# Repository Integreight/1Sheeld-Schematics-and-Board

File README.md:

# 1Sheeld Schematics, Board and Fritzing part files #

## Overview ##

This repository contains the schematics, board, and Fritzing part files for 1Sheeld board.

## Schematics Reference Image ##

## Board Reference Image ##

## Fritzing Part Reference Image ##

## Changelog ##

To see what has changed in recent versions of 1Sheeld Schematics and Board files, see the [Change Log](CHANGELOG.md).

## License and Copyright ##

```
These files are free; you can redistribute them and/or modify them under the
terms of the Creative Commons Attribution-ShareAlike 4.0 International
License only, as published by the Creative Commons organization.

These files are distributed in the hope that they will be useful, but
WITHOUT ANY WARRANTY; without even the implied warranty of MERCHANTABILITY
or FITNESS FOR A PARTICULAR PURPOSE.  See the Creative Commons Attribution-
ShareAlike 4.0 International License for more details (a copy is included
in the LICENSE file that accompanied these files).

Please contact Integreight, Inc. at info@integreight.com or post on our
support forums www.1sheeld.com/forum if you need additional information
or have any questions.
```

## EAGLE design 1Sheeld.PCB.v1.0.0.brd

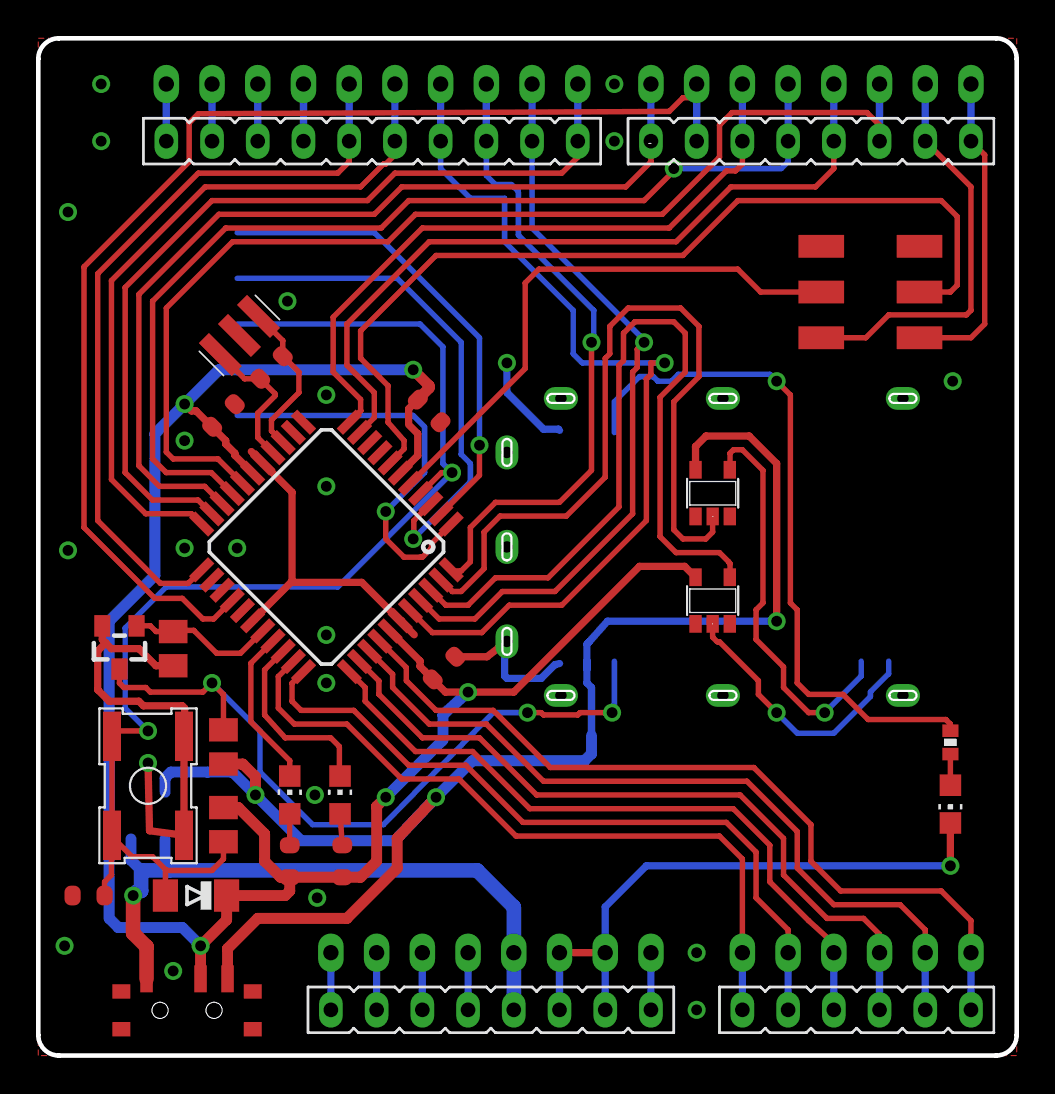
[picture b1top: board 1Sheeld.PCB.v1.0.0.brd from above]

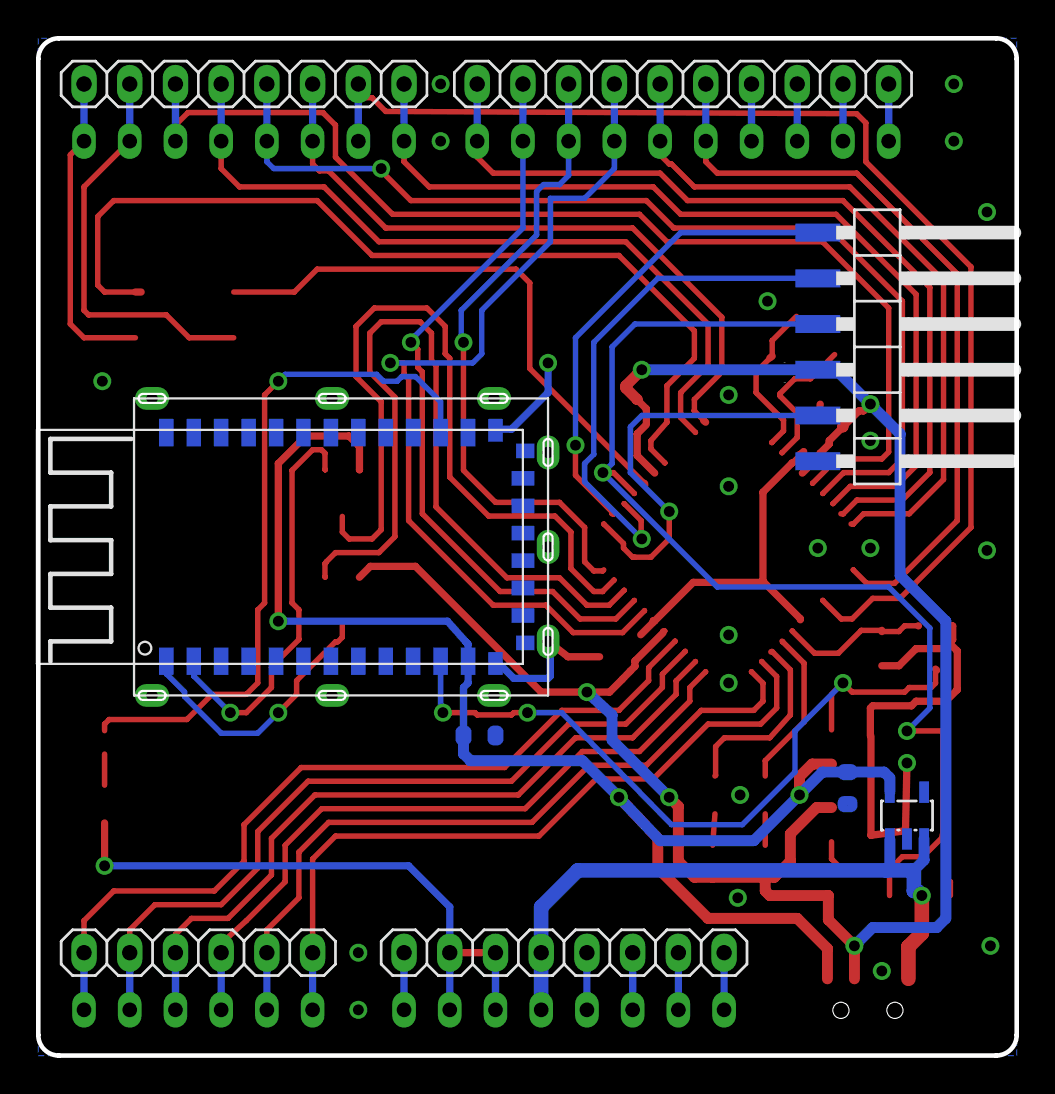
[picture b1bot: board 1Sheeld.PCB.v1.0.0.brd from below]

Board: 2 copper layers, 54.4 x 56.5 mm, 37 parts (10 on the bottom side), 52 nets.

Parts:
AD: M06-1; 1X06
AD1: FE06-1; FE06
BT-HC06: BLUETOOTH-SERIALSMD; SERIAL_BLUETEETH
BT-LED: BLUE; CHIP-LED0805
C1, C2, C3, C4, C6: 100nF; C0603-ROUND
C5: 1u; C0603-ROUND
D1: CD1206-S01575; MINIMELF
IC1, IC2: 74LVC1G125DBV; SOT23-5
ICSP: PINHD-1X06SMD; 1X06/90SMD
IOH: M10-1; 1X10
IOH1: FE10-1; FE10
IOL: M08-1; 1X08
IOL1: FE08-1; FE08
POWER: M08-1; 1X08
POWER1: FE08-1; FE08
POWER-SWITCH: MULTICOMP - MSS3-V-T/R; SWITCHMULTI
Q1: TN0201K; SOT23
R1: 4.7Kohm; M0805
R2: 1Mohm; R0603-ROUND
R3: 470ohm; 0402-RES
R4, R7: 10Kohm; M0805
R8, R9: 1Kohm; R0603-ROUND
RESET: SWITCHOMRON; OMRONSWITCH
RXD: YELLOW; CHIP-LED0805
S1: Metal shield; BT_SHIELD
TXD: GREEN; CHIP-LED0805
U1: LP2985-33DBVR; SOT23-DBV
U2: ATmega162; TQFP44
UART-SW: SWITCH
Y1: CSTCR7M37G53-R0 7.37MHZ; CSTCR6M

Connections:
+3.3V: BT-HC06.12, C1.2, C5.2, IC1.5, POWER-SWITCH.3, R7.2, U1.5
+5V: POWER.5, POWER1.5, POWER-SWITCH.1, U1.1, U1.3
ARDUINO/3.3V: POWER.4, POWER1.4
ARDUINO/RESET: POWER.3, POWER1.3
BT-LED: BT-HC06.24, R3.2
BT-RESET: BT-HC06.11, Q1.3, R7.1
GND: BT-HC06.13, BT-HC06.22, BT-LED.C, C1.1, C2.1, C3.1, C4.1, C5.1, C6.1, IC1.1, IC1.3, IC2.1, IC2.3, ICSP.6, IOH.7, IOH1.7, POWER.6, POWER.7, POWER1.6, POWER1.7, POWER-SWITCH.P$4, POWER-SWITCH.P$5, POWER-SWITCH.P$6, POWER-SWITCH.P$7, Q1.2, R1.1, RESET.1, RESET.2, S1.S1, S1.S2, S1.S3, S1.S4, S1.S5, S1.S6, S1.S7, S1.S8, S1.S9, U1.2, U2.8, U2.9, U2.12, U2.13, U2.16, U2.24, U2.25, U2.27, U2.28, U2.39, Y1.2
IOREF: POWER.2, POWER1.2
unnamed: IOH.10, IOH1.10
unnamed: IOH.9, IOH1.9
unnamed: BT-LED.A, R3.1
unnamed: IOH.8, IOH1.8
unnamed: R9.1, TXD.A
unnamed: R8.1, RXD.A
N/A: POWER.1, POWER1.1
PA0/A5: AD.6, AD1.6, U2.37
PA1/A4: AD.5, AD1.5, U2.36
PA2/A3: AD.4, AD1.4, U2.35
PA3/A2: AD.3, AD1.3, U2.34
PA4/A1: AD.2, AD1.2, U2.33
PA5/A0: AD.1, AD1.1, U2.32
PA6/LED-RXD: RXD.C, U2.31
PA7/LED-TXD: TXD.C, U2.30
PB0/11: IOH.4, IOH1.4, U2.40
PB1/9: IOH.2, IOH1.2, U2.41
PB2/RXD1: IC2.4, U2.42
PB3/TXD1: IC1.2, U2.43
PB4/SS/10: IOH.3, IOH1.3, U2.44
PB5/MOSI: ICSP.5, U2.1
PB6/MISO: ICSP.1, U2.2
PB7/SCK: ICSP.2, U2.3
PC0/2: IOL.3, IOL1.3, U2.18
PC1/4: IOL.5, IOL1.5, U2.19
PC2/7: IOL.8, IOL1.8, U2.20
PC3/8: IOH.1, IOH1.1, U2.21
PC4/12: IOH.5, IOH1.5, U2.22
PC5/13: IOH.6, IOH1.6, U2.23
PD0/RXD: U2.5, UART-SW.5
PD1/TXD: U2.7, UART-SW.2
PD4/3: IOL.4, IOL1.4, U2.10
PD5/5: IOL.6, IOL1.6, U2.11
PE0: Q1.1, R1.2, U2.29
PE2/6: IOL.7, IOL1.7, U2.26
RESET: C6.2, D1.A, ICSP.3, R4.1, RESET.3, RESET.4, U2.4
RX/0: IOL.1, IOL1.1, UART-SW.1
TX/1: IOL.2, IOL1.2, UART-SW.4
UART-RX: BT-HC06.2, IC1.4
UART-TX: BT-HC06.1, IC2.2
VCC: C2.2, C3.2, C4.2, D1.C, IC2.5, ICSP.4, POWER-SWITCH.2, R4.2, R8.2, R9.2, U2.6, U2.17, U2.38
VIN: POWER.8, POWER1.8
XTAL1: R2.1, U2.15, Y1.3
XTAL2: R2.2, U2.14, Y1.1

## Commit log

2014-07-10 Edited the image in the README.md file
2015-10-19 Revamped the readme and added a changelog file
2015-10-19 Fixed a typo in the readme file
2015-10-22 Renamed the files to reflect the version number
2016-12-19 Updated the PCB, schematics and added the Fritzing part

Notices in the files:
parts and their libraries:
m-pad-2.1: License : GNU General Public License version 2 (see bottom)
